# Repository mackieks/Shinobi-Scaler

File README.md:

# Shinobi Scaler 1 (*OLD*) <picture> <source media="(prefers-color-scheme: dark)" srcset="images/logo_light.png">  </picture> 

Shinobi is a reimagined, miniaturized GBS8200 for portablizers. Like the original GBS8200, it can convert 240p and 480i RGBs to 480p/720p/960p/1080p VGA, making it perfect for connecting retro video game consoles to modern LCDs.

## Features
- [x] 47 x 57mm 2-layer PCB (designed in EAGLE)
- [x] Compatible with [rama's GBS-Control](https://github.com/ramapcsx2/gbs-control)
- [x] 240p/480i RGBs input; 480p/720p/960p/1080p RGBHV/VGA/YPbPr output
- [x] 0.1" PTHs for power and IO (can be mounted with pin headers on a carrier PCB)
- [x] TV5725 scaler IC and 64Mbit SDRAM from GBS8200
- [x] Integrated ESP8266 with PCB antenna
- [x] Integrated CH340C USB-Serial for programming
- [x] Integrated Si5351A clock generator
- [x] Draws 650mA @ 3.3V (2.15W) when scaling 240p to 480p
- [x] Power from 3.3V directly, or supply 4-15V to onboard high-current 3.3V regulator

## Gallery
Shinobi PCB

1Chip SNES RGBs upscaled to 640x480 VGA, displayed on ZJ050NA-08C LCD

## Ordering
Recommended fabrication specs:
- 1mm-thick 2-layer PCB
- ENIG finish
- Solderpaste stencil for top side highly recommended

**Note:** There are multiple revisions of the ESP-06 (ESP8266 module). Only the most recent revision is compatible with Shinobi. Make sure your ESP-06 has three "Wi-Fi lines" inside the A.I. Thinker logo circle, and that three of the four corner pads are *not* connected to GND. 

I maintain a [Mouser project](https://www.mouser.com/ProjectManager/ProjectDetail.aspx?AccessID=a0a4651c6a) with most of the BOM. Thanks to [biggestsonicfan](https://github.com/biggestsonicfan) for providing an equivalent [Digikey cart](https://digikey.com/short/t3m1vqz2)!

You will still need to source a TV5725, ESP-06, and CH340C elsewhere. Cheap GBS8200s are available from AliExpress, eBay, DHGate, and Amazon if you'd like to harvest the TV5725 and SDRAM from one. I get my [TV5725s](https://www.aliexpress.us/item/3256801105294792.html) and [CH340Cs](https://www.aliexpress.com/wholesale?&SearchText=ch340c) from AliExpress. ESP-06s can be obtained from [Eckstein-Shop](https://eckstein-shop.de/AI-Thinker-ESP8266-ESP-06-Serial-WIFI-Wireless-Remote-Control-Module).

**Update (11/3/22):** ESP-06s have been relisted on the AliExpress Keli-te Store.

**Update (1/25/23):** TPS621351RGXR is available for purchase on TI's website.

**Update (2/4/24):** TV5725 and ESP-06 links have been updated.

## Assembly
An ``ibom.html`` file exported via [InteractiveHtmlBom](https://github.com/openscopeproject/InteractiveHtmlBom) is included to facilitate assembly. Thanks, [biggestsonicfan](https://github.com/biggestsonicfan)!

As mentioned previously, you can harvest the TV5725 and SDRAM from a GBS-8200 if you'd like. Please note that previous advice to harvest the 0603 ferrite beads from the GBS-8200 is outdated. Use 220Ω @ 100MHz 0402 ferrite beads as called out in the BOM.

**Note:** There is an 0805 zero-ohm resistor (R19) in series with the output of the onboard 3.3V regulator. If you intend to power Shinobi from an external 3.3V supply, you can omit this resistor to avoid backfeeding the onboard 3.3V regulator. If you choose to remove the zero-ohm and/or U7 (TPS621351), the board will need to be powered with an external 3.3V supply during programming. 

## Programming
- Install [CH340 drivers](http://www.wch-ic.com/downloads/CH341SER_ZIP.html)
- Bridge the `prg` jumper with solder (or tweezers)
- Plug USB-C into Shinobi. **Note:** USB-C port works in both orientations on the latest board rev.
- Verify COM port (or your platform's equivalent) is enumerating
- Open GBS-Control release of your choice in Arduino IDE (these steps assume you have already installed requisite libraries, etc.)
- Set up Tools menu as shown, select CH340C port under Port menu, then program

- When programming is complete, unplug Shinobi, unbridge `prg`, and power back up to access GBS-Control Wi-Fi AP

## Undervolting

To undervolt Shinobi 1, do the following:
- [x] Replace R14 with an 0402 300k 1% resistor
- [x] Replace R15 with an 0402 787k 1% resistor
- [x] Replace U8 with LDL112PV15R 

This sets U7 to output 2.54V, and changes the DVDD rail to 1.5V. The LDO dropout is decreased from 1.5V (3.3->1.8) to only 1V (2.5->1.5). 

While this won't match Shinobi 2's power efficiency, it should still be a major improvement over a stock Shinobi 1.
  
## To-do
- [ ] Finish prototype enclosure and upload photos + MCAD files
- [ ] Run reliability tests for higher output resolutions (currently only 480P has been vetted)

## License
[Solderpad Hardware License v2.1](https://solderpad.org/licenses/SHL-2.1/)

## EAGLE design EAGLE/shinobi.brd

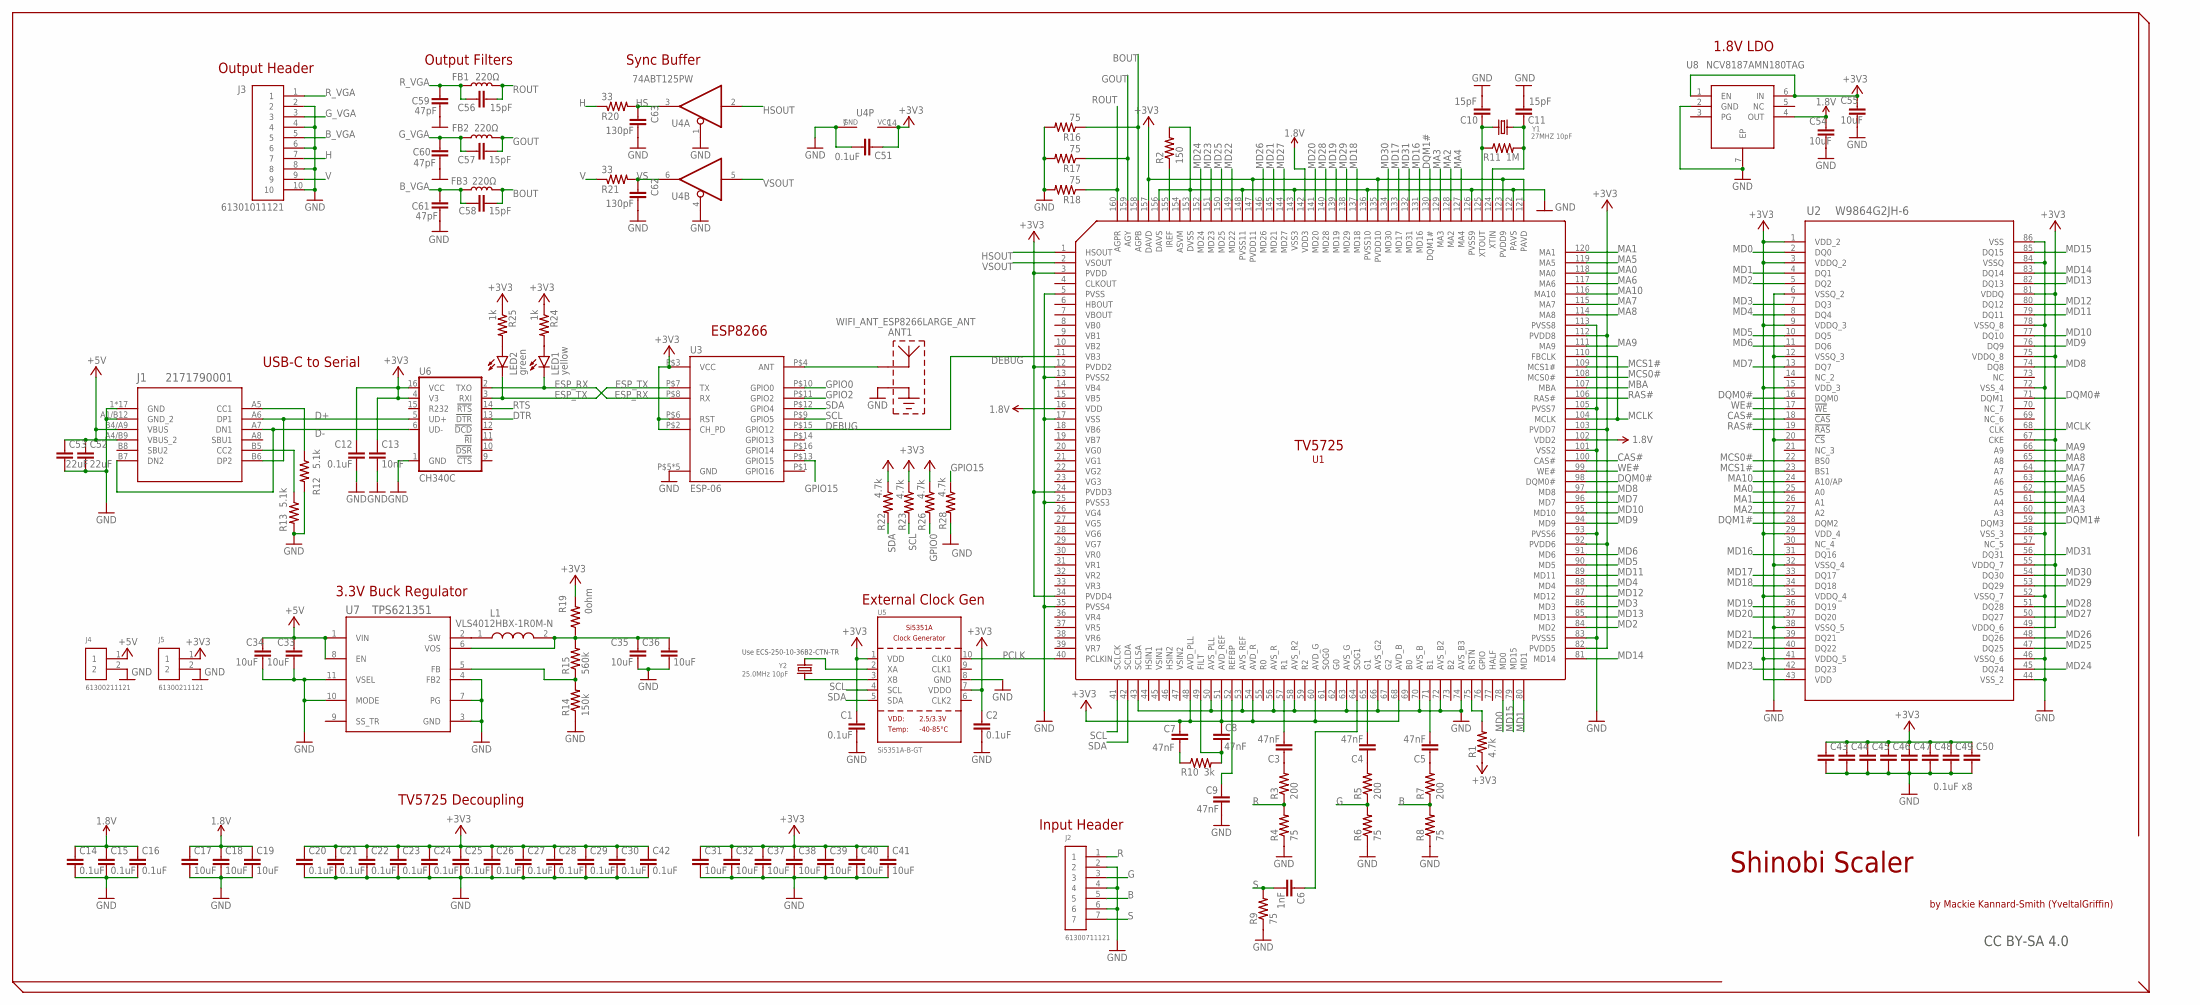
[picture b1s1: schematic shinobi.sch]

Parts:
ANT1: WIFI_ANT_ESP8266LARGE_ANT; ANTENNA
C1, C2, C12, C14, C15, C16, C20, C21, C22, C23, C24, C25, C26, C27, C28, C29, C30, C42, C43, C44, C45, C46, C47, C48, C49, C50, C51: 0.1uF; C0402
C3, C4, C5, C7, C8, C9: 47nF; C0402
C6: 1nF; C0402
C10, C11, C56, C57, C58: 15pF; C0402
C13: 10nF; C0402
C17, C18, C19, C31, C32, C33, C34, C35, C36, C37, C38, C39, C40, C41, C54, C55: 10uF; C0603
C52, C53: 22uF; C0805
C59, C60, C61: 47pF; C0402
C62, C63: 130pF; C0402
FB1, FB2, FB3: 220Ω; R0402
J1: 2171790001; 2171790001_MOL
J2: 61300711121
J3: 61301011121
J4, J5: 61300211121
L1: VLS4012HBX-1R0M-N; VLS4012
LED1: yellow; CHIP-LED0603
LED2: green; CHIP-LED0603
R1, R22, R23, R26, R28: 4.7k; R0402
R2: 150; R0402
R3, R5, R7: 200; R0402
R4, R6, R8, R9, R16, R17, R18: 75; R0402
R10: 3k; R0402
R11: 1M; R0402
R12, R13: 5.1k; R0402
R14: 150k; R0402
R15: 560k; R0402
R19: 0ohm; R0805
R20, R21: 33; R0402
R24, R25: 1k; R0402
U1: TV5725; PQFP160
U2: W9864G2JH-6; WIN_TSOP-86_WIN
U3: ESP-06
U4: 74ABT125PW; TSSOP14
U5: Si5351A-B-GT; MSOP10
U6: CH340C; SO016
U7: TPS621351; RGX0011A
U8: NCV8187AMN180TAG; SON95P300X300X95-7N
Y1: 27MHZ 10pF; CRYSTAL_2.5X2
Y2: 25.0MHz 10pF; CRYSTAL_2.5X2

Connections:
1.8V: C14.1, C15.1, C16.1, C17.1, C18.1, C19.1, C54.1, U1.16 (VDD), U1.102 (VDD2), U1.142 (VDD3), U8.4 (OUT)
+3V3: C1.1, C2.1, C7.2, C8.2, C12.1, C13.1, C20.1, C21.1, C22.1, C23.1, C24.1, C25.1, C26.1, C27.1, C28.1, C29.1, C30.1, C31.1, C32.1, C37.1, C38.1, C39.1, C40.1, C41.1, C42.1, C43.1, C44.1, C45.1, C46.1, C47.1, C48.1, C49.1, C50.1, C51.1, C55.1, J5.1, R1.1, R19.2, R22.1, R23.1, R24.1, R25.1, R26.1, U1.3 (PVDD), U1.12 (PVDD2), U1.24 (PVDD3), U1.34 (PVDD4), U1.48 (AVD_PLL), U1.51 (AVD_REF), U1.54 (AVD_R), U1.60 (AVD_G), U1.68 (AVD_B), U1.82 (PVDD5), U1.92 (PVDD6), U1.103 (PVDD7), U1.112 (PVDD8), U1.121 (PAVD), U1.123 (PVDD9), U1.135 (PVDD10), U1.147 (PVDD11), U1.157 (DAVD), U2.1 (VDD_2), U2.3 (VDDQ_2), U2.9 (VDDQ_3), U2.15 (VDD_3), U2.29 (VDD_4), U2.35 (VDDQ_4), U2.41 (VDDQ_5), U2.43 (VDD), U2.49 (VDDQ_6), U2.55 (VDDQ_7), U2.67 (CKE), U2.75 (VDDQ_8), U2.81 (VDDQ), U3.P$2 (CH_PD), U3.P$3 (VCC), U3.P$6 (RST), U4.14 (VCC), U5.1 (VDD), U5.7 (VDDO), U6.4 (V3), U6.16 (VCC), U8.1 (EN), U8.6 (IN)
+5V: C33.1, C34.1, C52.1, C53.1, J1.A4/B9 (VBUS_2), J1.B4/A9 (VBUS), J4.1, U7.1 (VIN), U7.8 (EN)
ANT: ANT1.P$2 (ANT), U3.P$4 (ANT)
B: J2.5, R7.1, R8.2
BOUT: C58.1, FB3.1, R16.1, U1.158 (AGPB)
B_VGA: C58.2, C61.1, FB3.2, J3.5
CAS#: U1.100 (CAS#), U2.18 (!CAS)
D+: J1.A6 (DP1), J1.B6 (DP2), U6.5 (UD+)
D-: J1.A7 (DN1), J1.B7 (DN2), U6.6 (UD-)
DEBUG: U1.11 (VB3), U3.P$15 (GPIO12)
DQM0#: U1.98 (DQM0#), U2.16 (DQM0), U2.71 (DQM1)
DQM1#: U1.130 (DQM1#), U2.28 (DQM2), U2.59 (DQM3)
DTR: U6.13 (!DTR)
ESP_RX: LED1.C, U3.P$8 (RX), U6.2 (TXO)
ESP_TX: LED2.C, U3.P$7 (TX), U6.3 (RXI)
G: J2.3, R5.1, R6.2
GND: ANT1.P$1 (GND), C1.2, C2.2, C9.1, C10.1, C11.1, C12.2, C13.2, C14.2, C15.2, C16.2, C17.2, C18.2, C19.2, C20.2, C21.2, C22.2, C23.2, C24.2, C25.2, C26.2, C27.2, C28.2, C29.2, C30.2, C31.2, C32.2, C33.2, C34.2, C35.2, C36.2, C37.2, C38.2, C39.2, C40.2, C41.2, C42.2, C43.2, C44.2, C45.2, C46.2, C47.2, C48.2, C49.2, C50.2, C51.2, C52.2, C53.2, C54.2, C55.2, C59.2, C60.2, C61.2, C62.2, C63.2, J1.1 (GND), J1.2 (GND), J1.3 (GND), J1.4 (GND), J1.13 (GND), J1.14 (GND), J1.15 (GND), J1.16 (GND), J1.A1/B12 (GND_2), J1.B1/A12 (GND), J1.S_1_H1 (GND), J1.S_1_H2 (GND), J1.S_2_H1 (GND), J1.S_2_H2 (GND), J1.S_3_H1 (GND), J1.S_3_H2 (GND), J1.S_4_H1 (GND), J1.S_4_H2 (GND), J2.2, J2.4, J2.6, J3.2, J3.4, J3.6, J3.8, J3.10, J4.2, J5.2, R2.2, R4.1, R6.1, R8.1, R9.1, R12.2, R13.2, R14.1, R16.2, R17.2, R18.2, R28.2, U1.5 (PVSS), U1.13 (PVSS2), U1.17 (VSS), U1.25 (PVSS3), U1.35 (PVSS4), U1.43 (SCLSA), U1.50 (AVS_PLL), U1.53 (AVS_REF), U1.56 (AVS_R), U1.58 (AVS_R2), U1.63 (AVS_G), U1.66 (AVS_G2), U1.70 (AVS_B), U1.72 (AVS_B2), U1.74 (AVS_B3), U1.83 (PVSS5), U1.93 (PVSS6), U1.101 (VSS2), U1.105 (PVSS7), U1.113 (PVSS8), U1.122 (PAVS), U1.126 (PVSS9), U1.136 (PVSS10), U1.143 (VSS3), U1.148 (PVSS11), U1.153 (DVSS), U1.156 (DAVS), U2.6 (VSSQ_2), U2.12 (VSSQ_3), U2.20 (!CS), U2.32 (VSSQ_4), U2.38 (VSSQ_5), U2.44 (VSS_2), U2.46 (VSSQ_6), U2.52 (VSSQ_7), U2.58 (VSS_3), U2.72 (VSS_4), U2.78 (VSSQ_8), U2.84 (VSSQ), U2.86 (VSS), U3.P$5 (GND), U3.P$17 (GND), U3.P$18 (GND), U3.P$19 (GND), U3.P$20 (GND), U4.1 (OE), U4.4 (OE), U4.7 (GND), U5.8 (GND), U6.1 (GND), U7.3 (GND), U7.4 (FB2), U7.7 (PG), U7.10 (MODE), U7.11 (VSEL), U8.2 (GND), U8.7 (EP)
GOUT: C57.1, FB2.1, R17.1, U1.159 (AGY)
GPIO0: R26.2, U3.P$10 (GPIO0)
GPIO2: U3.P$11 (GPIO2)
GPIO15: R28.1, U3.P$13 (GPIO15)
G_VGA: C57.2, C60.1, FB2.2, J3.3
H: J3.7, R20.1
HS: C63.1, R20.2, U4.3 (O)
HSOUT: U1.1 (HSOUT), U4.2 (I)
MA0: U1.118 (MA0), U2.25 (A0)
MA1: U1.120 (MA1), U2.26 (A1)
MA2: U1.128 (MA2), U2.27 (A2)
MA3: U1.129 (MA3), U2.60 (A3)
MA4: U1.127 (MA4), U2.61 (A4)
MA5: U1.119 (MA5), U2.62 (A5)
MA6: U1.117 (MA6), U2.63 (A6)
MA7: U1.115 (MA7), U2.64 (A7)
MA8: U1.114 (MA8), U2.65 (A8)
MA9: U1.111 (MA9), U2.66 (A9)
MA10: U1.116 (MA10), U2.24 (A10/AP)
MBA: U1.107 (MBA)
MCLK: U1.104 (MCLK), U1.110 (FBCLK), U2.68 (CLK)
MCS0#: U1.108 (MCS0#), U2.22 (BS0)
MCS1#: U1.109 (MCS1#), U2.23 (BS1)
MD0: U1.78 (MD0), U2.2 (DQ0)
MD1: U1.80 (MD1), U2.4 (DQ1)
MD2: U1.84 (MD2), U2.5 (DQ2)
MD3: U1.86 (MD3), U2.7 (DQ3)
MD4: U1.88 (MD4), U2.8 (DQ4)
MD5: U1.90 (MD5), U2.10 (DQ5)
MD6: U1.91 (MD6), U2.11 (DQ6)
MD7: U1.96 (MD7), U2.13 (DQ7)
MD8: U1.97 (MD8), U2.74 (DQ8)
MD9: U1.94 (MD9), U2.76 (DQ9)
MD10: U1.95 (MD10), U2.77 (DQ10)
MD11: U1.89 (MD11), U2.79 (DQ11)
MD12: U1.87 (MD12), U2.80 (DQ12)
MD13: U1.85 (MD13), U2.82 (DQ13)
MD14: U1.81 (MD14), U2.83 (DQ14)
MD15: U1.79 (MD15), U2.85 (DQ15)
MD16: U1.131 (MD16), U2.31 (DQ16)
MD17: U1.133 (MD17), U2.33 (DQ17)
MD18: U1.137 (MD18), U2.34 (DQ18)
MD19: U1.139 (MD19), U2.36 (DQ19)
MD20: U1.141 (MD20), U2.37 (DQ20)
MD21: U1.145 (MD21), U2.39 (DQ21)
MD22: U1.149 (MD22), U2.40 (DQ22)
MD23: U1.151 (MD23), U2.42 (DQ23)
MD24: U1.152 (MD24), U2.45 (DQ24)
MD25: U1.150 (MD25), U2.47 (DQ25)
MD26: U1.146 (MD26), U2.48 (DQ26)
MD27: U1.144 (MD27), U2.50 (DQ27)
MD28: U1.140 (MD28), U2.51 (DQ28)
MD29: U1.138 (MD29), U2.53 (DQ29)
MD30: U1.134 (MD30), U2.54 (DQ30)
MD31: U1.132 (MD31), U2.56 (DQ31)
unnamed: U5.3 (XB), Y2.1
unnamed: U5.2 (XA), Y2.3 (2)
unnamed: R1.2, U1.75 (RSTN)
unnamed: R2.1, U1.155 (IREF)
unnamed: C3.1, R3.2
unnamed: C10.2, R11.1, U1.125 (XTOUT), Y1.1
unnamed: C4.1, R5.2
unnamed: C3.2, U1.57 (R1)
unnamed: C4.2, U1.65 (G1)
unnamed: C5.1, R7.2
unnamed: C5.2, U1.71 (B1)
unnamed: C6.1, U1.64 (SOG1)
unnamed: C8.1, R10.2, U1.49 (FILT)
unnamed: C7.1, R10.1
unnamed: C9.2, U1.52 (REFBP)
unnamed: C11.2, R11.2, U1.124 (XTIN), Y1.3 (2)
unnamed: L1.1, U7.2 (SW)
unnamed: R14.2, R15.1, U7.5 (FB)
unnamed: C35.1, C36.1, L1.2, R15.2, R19.1, U7.6 (VOS)
unnamed: LED1.A, R24.2
unnamed: J1.A5 (CC1), R12.1
unnamed: J1.B5 (CC2), R13.1
unnamed: LED2.A, R25.2
PCLK: U1.40 (PCLKIN), U5.10 (CLK0)
R: J2.1, R3.1, R4.2
RAS#: U1.106 (RAS#), U2.19 (!RAS)
ROUT: C56.1, FB1.1, R18.1, U1.160 (AGPR)
RTS: U6.14 (!RTS)
R_VGA: C56.2, C59.1, FB1.2, J3.1
S: C6.2, J2.7, R9.2
SCL: R23.2, U1.41 (SCLCK), U3.P$9 (GPIO5), U5.4 (SCL)
SDA: R22.2, U1.42 (SCLDA), U3.P$12 (GPIO4), U5.5 (SDA)
V: J3.9, R21.1
VS: C62.1, R21.2, U4.6 (O)
VSOUT: U1.2 (VSOUT), U4.5 (I)
WE#: U1.99 (WE#), U2.17 (!WE)

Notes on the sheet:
Use ECS-250-10-36B2-CTN-TR
USB-C to Serial
External Clock Gen
Input Header
Output Header
1.8V LDO
3.3V Buck Regulator
ESP8266
Sync Buffer
Output Filters
TV5725 Decoupling
Shinobi Scaler
by Mackie Kannard-Smith (YveltalGriffin)
CC BY-SA 4.0

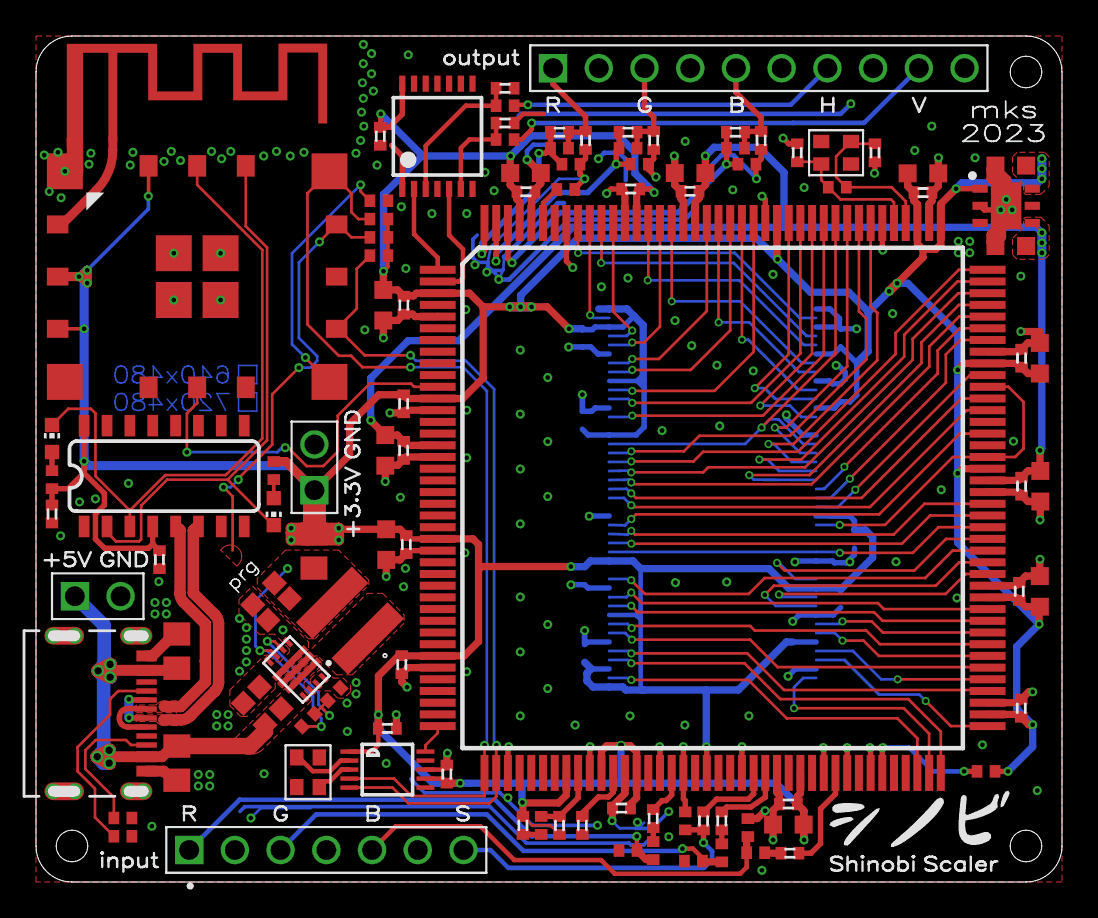
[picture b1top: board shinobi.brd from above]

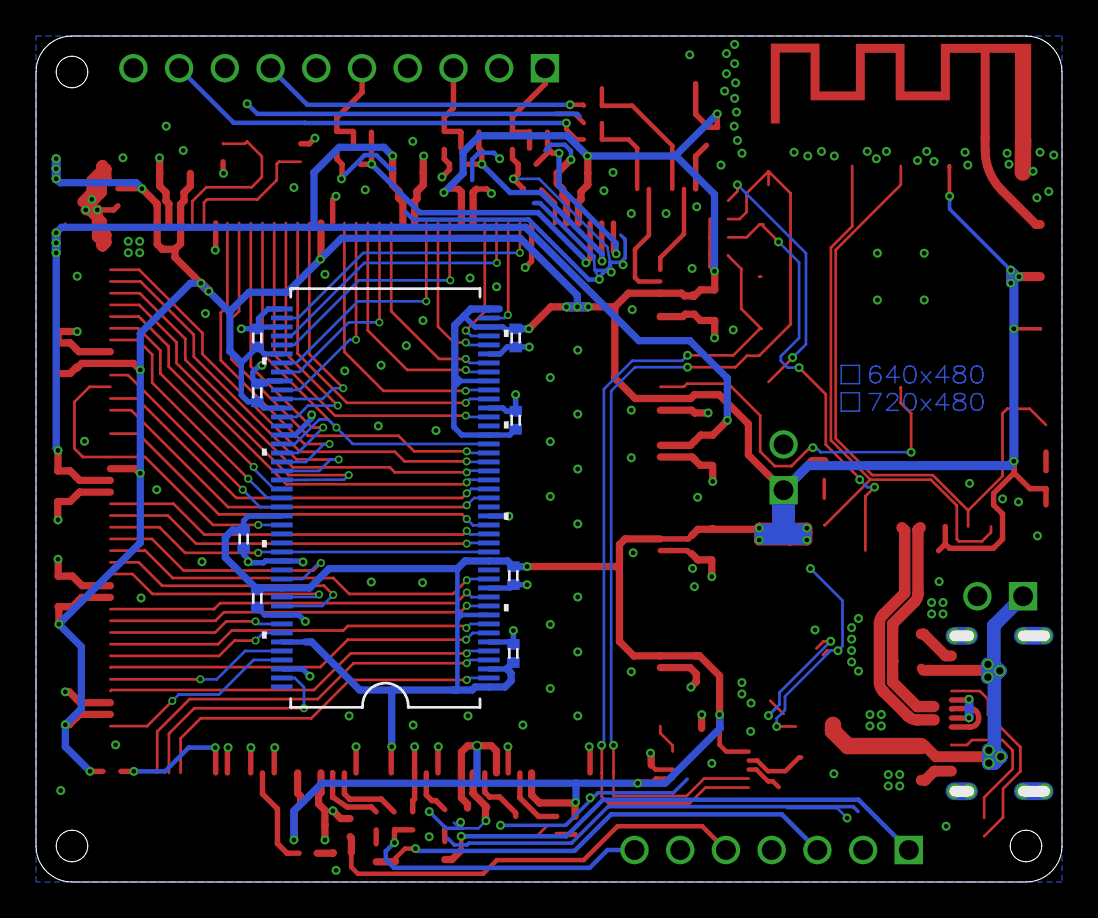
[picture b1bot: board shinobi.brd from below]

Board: 2 copper layers, 57.0 x 47.0 mm, 112 parts (9 on the bottom side), 105 nets.

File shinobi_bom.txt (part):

Partlist

Exported from shinobi.sch at 10/26/2022 5:39 PM

EAGLE Version 9.6.2 Copyright (c) 1988-2020 Autodesk, Inc.

Part     Value                     Device                    Package             Library           Sheet
C1       0.1uF                     C-USC0402                 C0402               resistor          1
C2       0.1uF                     C-USC0402                 C0402               resistor          1
C3       47nF                      C-USC0402                 C0402               resistor          1
C4       47nF                      C-USC0402                 C0402               resistor          1
C5       47nF                      C-USC0402                 C0402               resistor          1
C6       1nF                       C-USC0402                 C0402               resistor          1
C7       47nF                      C-USC0402                 C0402               resistor          1
C8       47nF                      C-USC0402                 C0402               resistor          1
C9       47nF                      C-USC0402                 C0402               resistor          1
C10      15pF                      C-USC0402                 C0402               resistor          1
C11      15pF                      C-USC0402                 C0402               resistor          1
C12      0.1uF                     C-USC0402                 C0402               resistor          1
C13      10nF                      C-USC0402                 C0402               resistor          1
C14      0.1uF                     C-USC0402                 C0402               resistor          1
C15      0.1uF                     C-USC0402                 C0402               resistor          1
C16      0.1uF                     C-USC0402                 C0402               resistor          1
C17      10uF                      C-USC0603                 C0603               resistor          1
C18      10uF                      C-USC0603                 C0603               resistor          1
C19      10uF                      C-USC0603                 C0603               resistor          1
C20      0.1uF                     C-USC0402                 C0402               resistor          1
C21      0.1uF                     C-USC0402                 C0402               resistor          1
C22      0.1uF                     C-USC0402                 C0402               resistor          1
C23      0.1uF                     C-USC0402                 C0402               resistor          1
C24      0.1uF                     C-USC0402                 C0402               resistor          1
C25      0.1uF                     C-USC0402                 C0402               resistor          1
C26      0.1uF                     C-USC0402                 C0402               resistor          1
C27      0.1uF                     C-USC0402                 C0402               resistor          1
C28      0.1uF                     C-USC0402                 C0402               resistor          1
C29      0.1uF                     C-USC0402                 C0402               resistor          1
C30      0.1uF                     C-USC0402                 C0402               resistor          1
C31      10uF                      C-USC0603                 C0603               resistor          1
C32      10uF                      C-USC0603                 C0603               resistor          1
C33      10uF                      C-USC0603                 C0603               resistor          1
C34      10uF                      C-USC0603                 C0603               resistor          1
C35      10uF                      C-USC0603                 C0603               resistor          1
C36      10uF                      C-USC0603                 C0603               resistor          1
C37      10uF                      C-USC0603                 C0603               resistor          1
C38      10uF                      C-USC0603                 C0603               resistor          1
C39      10uF                      C-USC0603                 C0603               resistor          1
C40      10uF                      C-USC0603                 C0603               resistor          1
C41      10uF                      C-USC0603                 C0603               resistor          1
C42      0.1uF                     C-USC0402                 C0402               resistor          1
C43      0.1uF                     C-USC0402                 C0402               resistor          1
C44      0.1uF                     C-USC0402                 C0402               resistor          1
C45      0.1uF                     C-USC0402                 C0402               resistor          1
C46      0.1uF                     C-USC0402                 C0402               resistor          1
C47      0.1uF                     C-USC0402                 C0402               resistor          1
C48      0.1uF                     C-USC0402                 C0402               resistor          1
C49      0.1uF                     C-USC0402                 C0402               resistor          1
C50      0.1uF                     C-USC0402                 C0402               resistor          1
C51      0.1uF                     C-USC0402                 C0402               resistor          1
C52      22uF                      C-USC0805                 C0805               resistor          1
C53      22uF                      C-USC0805                 C0805               resistor          1
C54      10uF                      C-USC0603                 C0603               resistor          1
C55      10uF                      C-USC0603                 C0603               resistor          1
C56      15pF                      C-USC0402                 C0402               resistor          1
C57      15pF                      C-USC0402                 C0402               resistor          1
C58      15pF                      C-USC0402                 C0402               resistor          1
C59      47pF                      C-USC0402                 C0402               resistor          1
C60      47pF                      C-USC0402                 C0402               resistor          1
C61      47pF                      C-USC0402                 C0402               resistor          1
C62      130pF                     C-USC0402                 C0402               resistor          1
C63      130pF                     C-USC0402                 C0402               resistor          1
FB1      220Ω                      L0402                     R0402               resistor          1
FB1      220Ω                      L0402                     R0402               resistor          1
FB1      220Ω                      L0402                     R0402               resistor          1
L1       VLS4012HBX-1R0M-N         VLS4012HBX-1R0M-N         VLS4012             SamacSys_Parts    1
LED1     yellow                    LEDCHIP-LED0603           CHIP-LED0603        led               1
LED2     green                     LEDCHIP-LED0603           CHIP-LED0603        led               1
R1       4.7k                      R-US_R0402                R0402               resistor          1
R2       150                       R-US_R0402                R0402               resistor          1
R3       200                       R-US_R0402                R0402               resistor          1
R4       75                        R-US_R0402                R0402               resistor          1
R5       200                       R-US_R0402                R0402               resistor          1
R6       75                        R-US_R0402                R0402               resistor          1
R7       200                       R-US_R0402                R0402               resistor          1
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
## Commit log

2022-10-24 Create LICENSE
2022-10-24 add source files
2022-10-24 update images
2022-10-25 update images, add eagle palette script
2022-10-25 add image and dxf
2022-10-25 fix ibom
2022-10-25 fix gerber issue, update schematic.png
2022-10-27 add demo photos
2022-12-05 Add MCAD (unfinished)
    -PCB STEP
    -Unfinished case file
2023-03-17 update board
2023-03-18 update brd
2023-07-21 update with correct ferrite beads
2023-07-25 Update LICENSE
2023-09-20 board update
    - minor tweak to cap placement (fixes soldermask aperture issue)
    -gerbers updated
    -iBOM updated
2024-01-23 update to solderpad license
2024-02-04 Update iBom and README
    Updates iBom to use InteractiveHtmlBom and edited README to include updated links to sourced components. Also updated my attribution to link to my github instead of twitter.
2024-07-17 WIP Shinobi 2
2024-07-18 shinobi2 routing
2024-07-18 Update PCB and BOM
2024-10-23 embed fonts, layout tweaks
2024-10-23 more minor layout tweaks
2024-10-23 tweak artwork
2024-10-28 small updates
2024-10-28 updating files
2024-10-28 update imgs
2024-10-28 add imgs

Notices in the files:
parts and their libraries:
microbuilder: This work is placed in the public domain, and may be freely used for commercial and non-commercial work with the following conditions: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
SparkFun-IC-Comms: Licensing: Creative Commons ShareAlike 4.0 International - https://creativecommons.org/licenses/by-sa/4.0
